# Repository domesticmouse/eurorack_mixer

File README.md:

# Eurorack Mixer

This is a Eurorack module for mixing signals, using a
[TL074](https://www.ti.com/product/TL074).
It is based on the ES x MKI mixer.

**Note:** This is a learning exercise.

[KiCanvas rendering of the mainboard](https://kicanvas.org/?github=https%3A%2F%2Fgithub.com%2Fdomesticmouse%2Feurorack_mixer%2Ftree%2Fmain%2Fhardware%2Fmainboard)

## Parts

| LCSC Part | Name | Description |
| --- | --- | --- |
| [C55071](https://www.lcsc.com/product-detail/C55071.html) | BOURNS 3224W-1-203E | POT 20kΩ 250mW SMD-3P,4.8x3.5mm |
| [C12594](https://www.lcsc.com/product-detail/C12594.html) | TI TL074CDR | LOW-NOISE JFET-INPUT OPERATIONAL AMPLIFIERS |
| [C311666](https://www.lcsc.com/product-detail/C311666.html) | Lelon OVK470M1ETR-0606 | CAP ALUM POLY 47uF ±20% 25V SMD |
| [C49678](https://www.lcsc.com/product-detail/C49678.html) | YAGEO CC0805KRX7R9BB104 | CAP CER 100nF 50V X7R 0805 |
| [C64982](https://www.lcsc.com/product-detail/C64982.html) | MDD(Microdiode Semiconductor) B340A | DIODE SCHOTTKY 40V SMA(DO-214AC) |
| [C19171391](https://www.lcsc.com/product-detail/C19171391.html) | YONGYUTAI YLED0805R | LED RED 0805 SMD |
| [C82544](https://www.lcsc.com/product-detail/C82544.html) | DIODES 1N5819HW-7-F | 25A 1 Independent 40V 450mV@1A 1A SOD-123 Single Diodes |
| [C573025](https://www.lcsc.com/product-detail/C573025.html) | Eurorack Power Connector | CONN IDC HEADER TH 10POS 2.54mm |
| [C17513](https://www.lcsc.com/product-detail/C17513.html) | UNI-ROYAL 0805W8F1001T5E | RES 1kΩ ±1% 125mW 0805 |
| [C149504](https://www.lcsc.com/product-detail/C149504.html) | UNI-ROYAL 0805W8F1003T5E | RES 100kΩ ±1% 125mW 0805 |
| [C17593](https://www.lcsc.com/product-detail/C17593.html) | UNI-ROYAL 0805W8F2702T5E | RES 27kΩ ±1% 125mW 0805 |
| [C17903](https://www.lcsc.com/product-detail/C17903.html) | UNI-ROYAL 1206W4F100JT5E | RES 10Ω ±1% 250mW 1206 |

## Sources

- [AI002 DIY Synthesizer Mixer Module Build Guide](https://aisynthesis.com/ai002-diy-eurorack-mixer-module-build/)
- [AI002 Schematic](https://aisynthesis.com/wp-content/uploads/2018/10/AI002-Mixer-Schematic-2.pdf)
- [ES x MKI EDU DIY Mixer](https://www.ericasynths.lv/shop/diy-kits-1/edu-diy-mixer/)
- [ES x MKI EDU DIY Mixer Manual](https://www.ericasynths.lv/media/MIXER_MANUAL.pdf)
- [Moritz Klein](https://www.youtube.com/@MoritzKlein0)'s
  [Designing a 3-channel mixer with diode distortion from scratch](https://www.youtube.com/watch?v=q8tmUgaXrEQ)
- [TL074 data sheet](https://www.ti.com/lit/ds/symlink/tl074.pdf)
- [EuroRack dimensions](https://midisoft.de/EuroRackDimensions/EuroRack_Dimensions.html)
- [Eurorack Panel Dimensions](https://www.exploding-shed.com/manuals-tutorials/manuals/standards-of-eurorack/eurorack-dimensions/)
- [Doepfer A100 DIY](https://doepfer.de/DIY/a100_diy.htm)
- [benjiaomodular](https://benjiaomodular.com/)'s [MiniAttenuMix](https://benjiaomodular.com/post/2023-11-08-miniattenumix/)

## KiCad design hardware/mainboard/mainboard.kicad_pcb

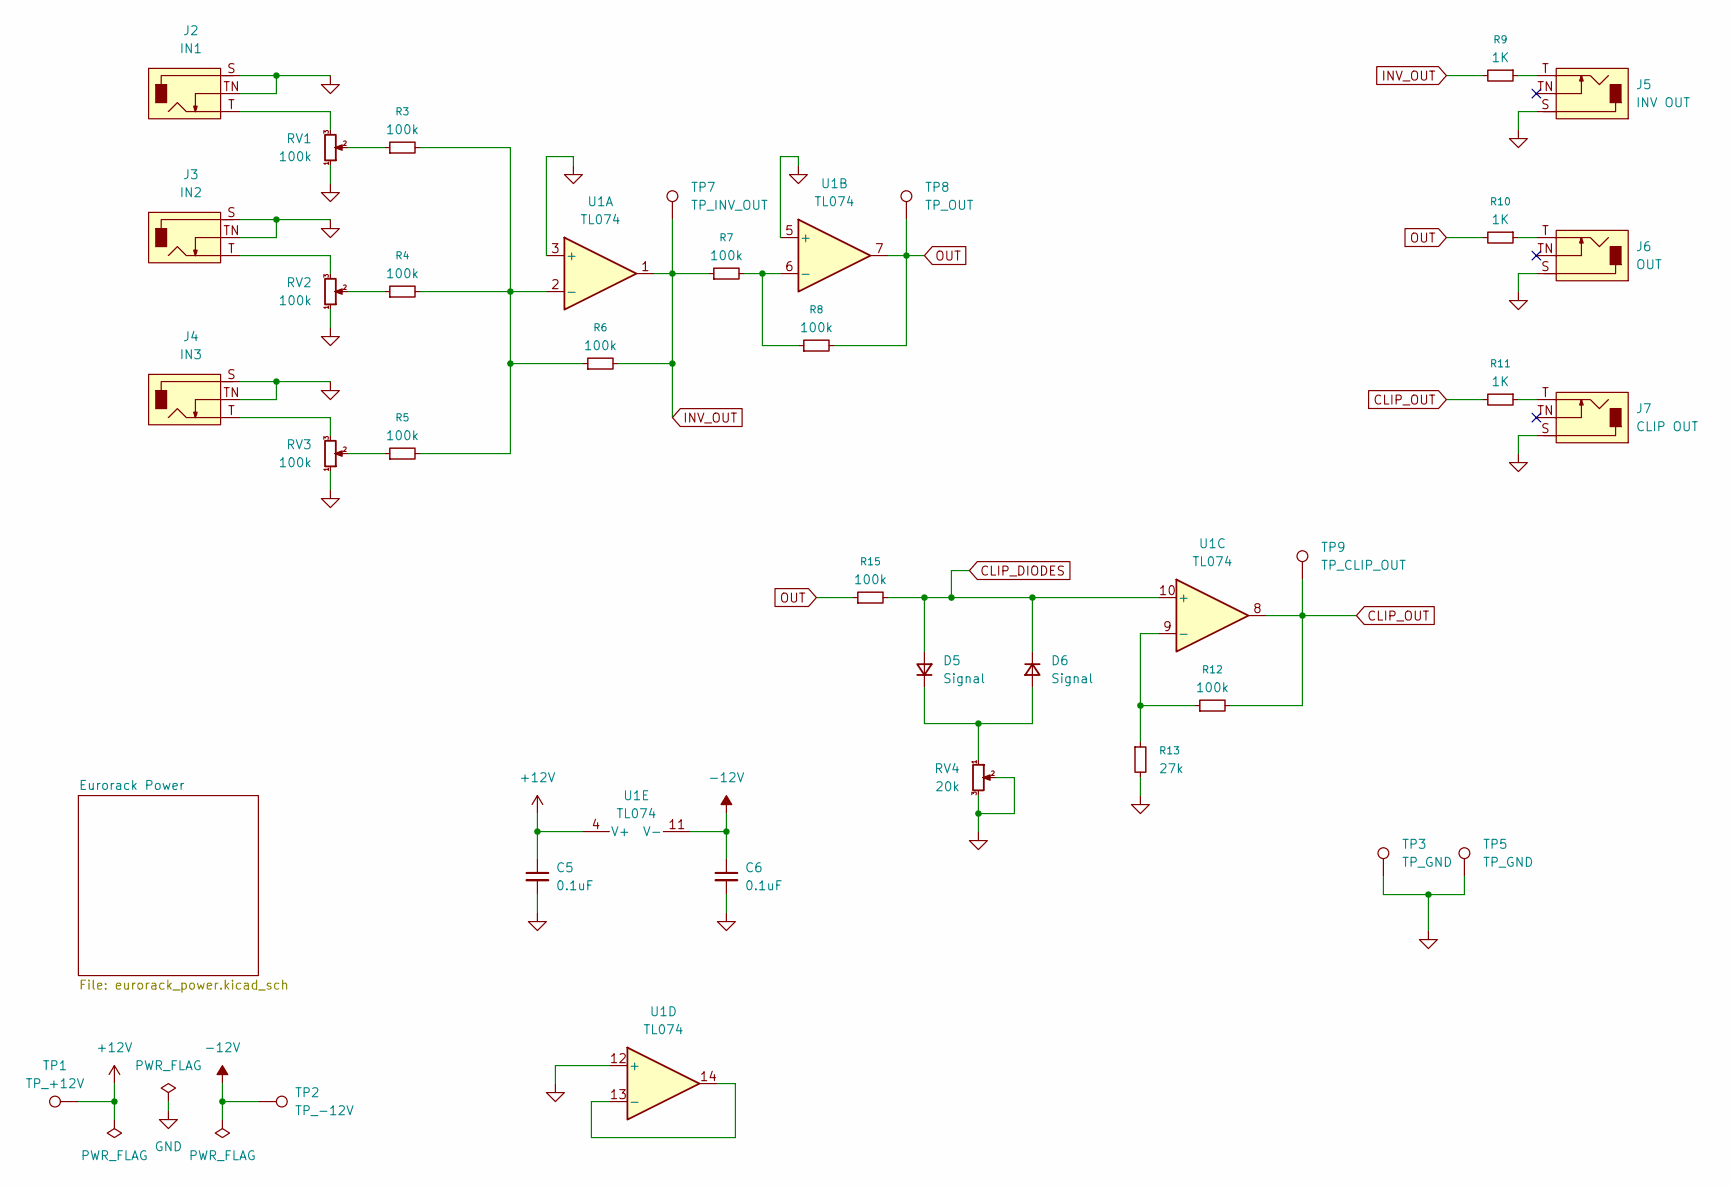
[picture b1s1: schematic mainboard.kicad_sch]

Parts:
C5, C6: 0.1uF; C_0805_2012Metric_Pad1.18x1.45mm_HandSolder; Manufacturer_Part_No CC0805KRX7R9BB104; LCSC_Part_No C49678
D5, D6: Signal; D_SOD-123; Manufacturer_Part_No 1N5819HW-7-F; LCSC_Part_No C82544
J2: IN1; Jack_3.5mm_WQP-PJ398SM_Vertical_Tight
J3: IN2; Jack_3.5mm_WQP-PJ398SM_Vertical_Tight
J4: IN3; Jack_3.5mm_WQP-PJ398SM_Vertical_Tight
J5: INV OUT; Jack_3.5mm_WQP-PJ398SM_Vertical_Tight
J6: OUT; Jack_3.5mm_WQP-PJ398SM_Vertical_Tight
J7: CLIP OUT; Jack_3.5mm_WQP-PJ398SM_Vertical_Tight
R3, R4, R5, R6, R7, R8, R12, R15: 100k; R_0805_2012Metric_Pad1.20x1.40mm_HandSolder; Manufacturer_Part_No 0805W8F1003T5E; LCSC_Part_No C149504
R9, R10, R11: 1K; R_0805_2012Metric_Pad1.20x1.40mm_HandSolder; Manufacturer_Part_No 0805W8F1001T5E; LCSC_Part_No C17513
R13: 27k; R_0805_2012Metric_Pad1.20x1.40mm_HandSolder; Manufacturer_Part_No 0805W8F2702T5E; LCSC_Part_No C17593
RV1, RV2, RV3: 100k; Potentiometer_Alpha_RD901F-40-00D_Single_Vertical
RV4: 20k; Potentiometer_Bourns_3224W_Vertical; Manufacturer_Part_No 3224W-1-203E; LCSC_Part_No C55071
TP1: TP_+12V; TestPoint_Keystone_5000-5004_Miniature; Manufacturer_Part_No RH-5001; LCSC_Part_No C5199801
TP2: TP_-12V; TestPoint_Keystone_5000-5004_Miniature; Manufacturer_Part_No RH-5001; LCSC_Part_No C5199801
TP3, TP5: TP_GND; TestPoint_Keystone_5000-5004_Miniature; Manufacturer_Part_No RH-5001; LCSC_Part_No C5199801
TP7: TP_INV_OUT; TestPoint_Keystone_5000-5004_Miniature; Manufacturer_Part_No RH-5001; LCSC_Part_No C5199801
TP8: TP_OUT; TestPoint_Keystone_5000-5004_Miniature; Manufacturer_Part_No RH-5001; LCSC_Part_No C5199801
TP9: TP_CLIP_OUT; TestPoint_Keystone_5000-5004_Miniature; Manufacturer_Part_No RH-5001; LCSC_Part_No C5199801
U1: TL074; SOIC-14_3.9x8.7mm_P1.27mm; Manufacturer_Part_No TL074CDR; LCSC_Part_No C12594

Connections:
+12V: C5.1, TP1.1, U1.4 (V+); also elsewhere on the board
-12V: C6.1, TP2.1, U1.11 (V-); also elsewhere on the board
CLIP_DIODES: D5.2 (A), D6.1 (K), R15.2, U1.10 (+)
CLIP_OUT: R11.2, R12.2, TP9.1, U1.8
GND: C5.2, C6.2, J2.S, J2.TN, J3.S, J3.TN, J4.S, J4.TN, J5.S, J6.S, J7.S, R13.2, RV1.1, RV2.1, RV3.1, RV4.2, RV4.3, TP3.1, TP5.1, U1.3 (+), U1.5 (+), U1.12 (+); also elsewhere on the board
INV_OUT: R6.2, R7.1, R9.2, TP7.1, U1.1
unnamed: D5.1 (K), D6.2 (A), RV4.1
unnamed: J2.T, RV1.3
unnamed: J3.T, RV2.3
unnamed: J4.T, RV3.3
unnamed: J5.T, R9.1
unnamed: J6.T, R10.1
unnamed: J7.T, R11.1
unnamed: R3.1, RV1.2
unnamed: R4.1, RV2.2
unnamed: R5.1, RV3.2
unnamed: R3.2, R4.2, R5.2, R6.1, U1.2 (-)
unnamed: R7.2, R8.1, U1.6 (-)
unnamed: R12.1, R13.1, U1.9 (-)
unnamed: U1.13 (-), U1.14
OUT: R8.2, R10.2, R15.1, TP8.1, U1.7

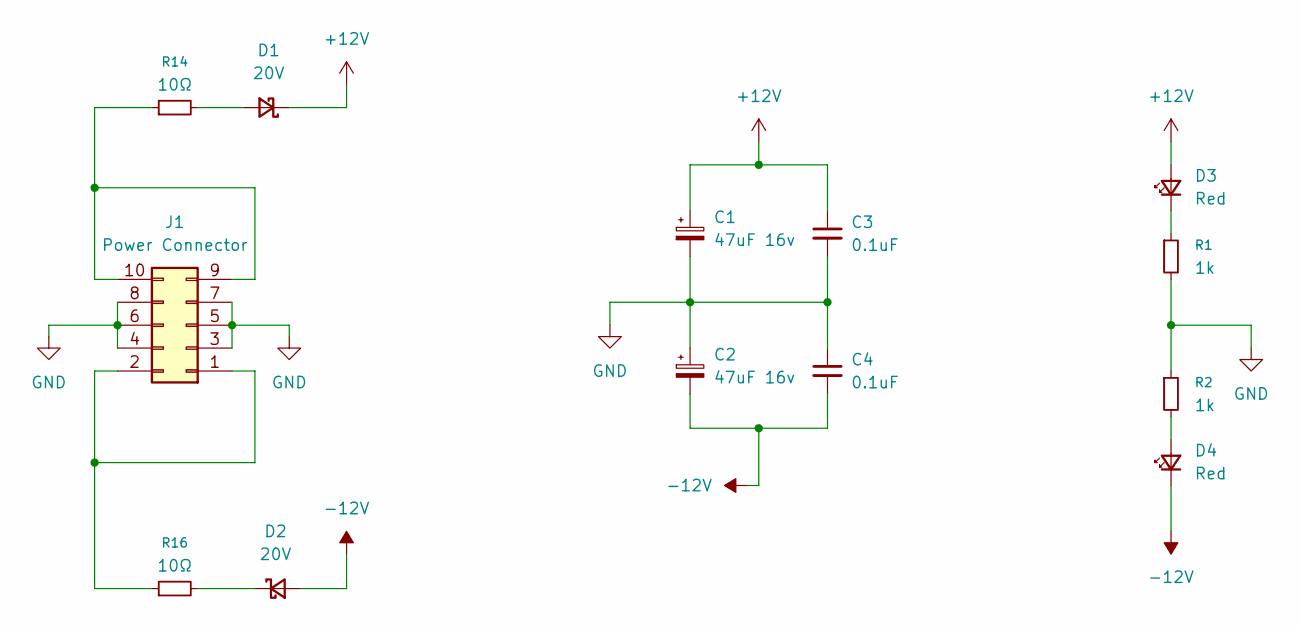
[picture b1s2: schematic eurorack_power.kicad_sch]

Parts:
C1, C2: 47uF 16v; CP_Elec_6.3x5.9; Manufacturer_Part_No OVK470M1ETR-0606; LCSC_Part_No C311666
C3, C4: 0.1uF; C_0805_2012Metric_Pad1.18x1.45mm_HandSolder; Manufacturer_Part_No CC0805KRX7R9BB104; LCSC_Part_No C49678
D1, D2: 20V; D_SOD-323F; Manufacturer_Part_No BAT46WJ,115; LCSC_Part_No C114696
D3, D4: Red; LED_0805_2012Metric_Pad1.15x1.40mm_HandSolder; Manufacturer_Part_No YLED0805R; LCSC_Part_No C19171391
J1: Power Connector; IDC-Header_2x05_P2.54mm_Vertical; Manufacturer_Part_No 1761681-3; LCSC_Part_No C573025
R1, R2: 1k; R_0805_2012Metric_Pad1.20x1.40mm_HandSolder; Manufacturer_Part_No 0805W8F1001T5E; LCSC_Part_No C17513
R14, R16: 10Ω; R_1206_3216Metric_Pad1.30x1.75mm_HandSolder

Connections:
+12V: C1.1, C3.1, D1.1 (K), D3.2 (A); also elsewhere on the board
-12V: C2.2, C4.2, D2.2 (A), D4.1 (K); also elsewhere on the board
GND: C1.2, C2.1, C3.2, C4.1, J1.3, J1.4, J1.5, J1.6, J1.7, J1.8, R1.2, R2.1; also elsewhere on the board
unnamed: D1.2 (A), R14.2
unnamed: D2.1 (K), R16.2
unnamed: D3.1 (K), R1.1
unnamed: D4.2 (A), R2.2
unnamed: J1.1, J1.2, R16.1
unnamed: J1.9, J1.10, R14.1

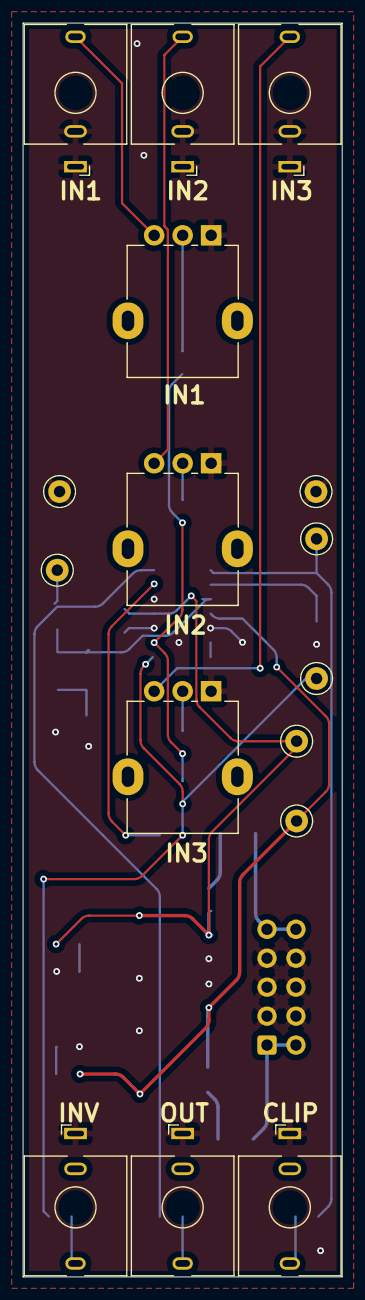
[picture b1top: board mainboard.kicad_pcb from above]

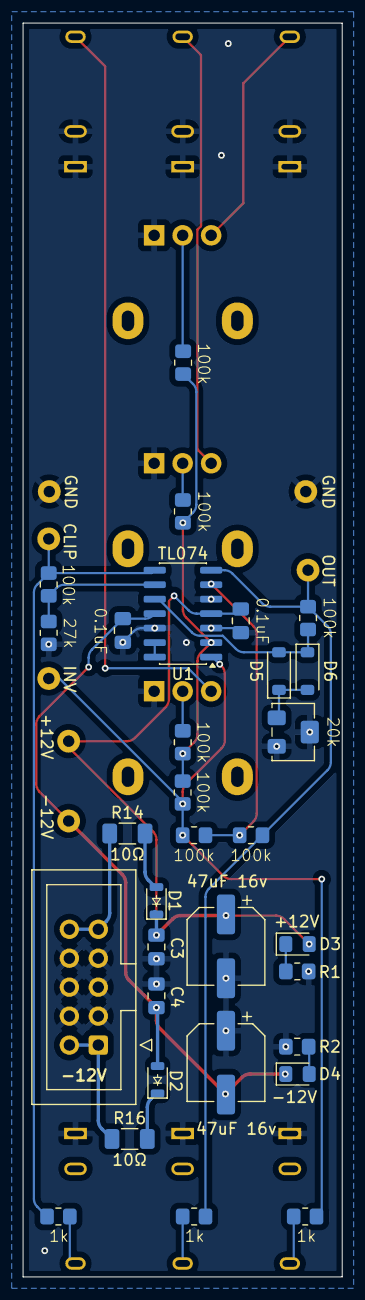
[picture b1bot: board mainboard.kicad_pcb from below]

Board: 2 copper layers, 28.0 x 110.0 mm, 47 parts (31 on the bottom side), 27 nets.

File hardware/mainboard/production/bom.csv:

Designator,Footprint,Quantity,Value,LCSC Part #
"C1, C2",CP_Elec_6.3x5.9,2,47uF 16v,
"C3, C4, C5, C6",0805,4,0.1uF,
"D1, D2",D_SOD-323F,2,20V,
"D3, D4",0805,2,Red,
"D5, D6",D_SOD-123,2,Signal,
J1,IDC-Header_2x05_P2.54mm_Vertical,1,Power Connector,
"R1, R10, R11, R2, R9",0805,5,1k,
"R12, R15, R3, R4, R5, R6, R7, R8",0805,8,100k,
R13,0805,1,27k,
"R14, R16",1206,2,10Ω,
RV4,Potentiometer_Bourns_3224W_Vertical,1,20k,
TP1,TestPoint_Keystone_5000-5004_Miniature,1,TP_+12V,
TP2,TestPoint_Keystone_5000-5004_Miniature,1,TP_-12V,
"TP3, TP5",TestPoint_Keystone_5000-5004_Miniature,2,TP_GND,
TP7,TestPoint_Keystone_5000-5004_Miniature,1,TP_INV_OUT,
TP8,TestPoint_Keystone_5000-5004_Miniature,1,TP_OUT,
TP9,TestPoint_Keystone_5000-5004_Miniature,1,TP_CLIP_OUT,
U1,SOIC-14_3.9x8.7mm_P1.27mm,1,TL074,

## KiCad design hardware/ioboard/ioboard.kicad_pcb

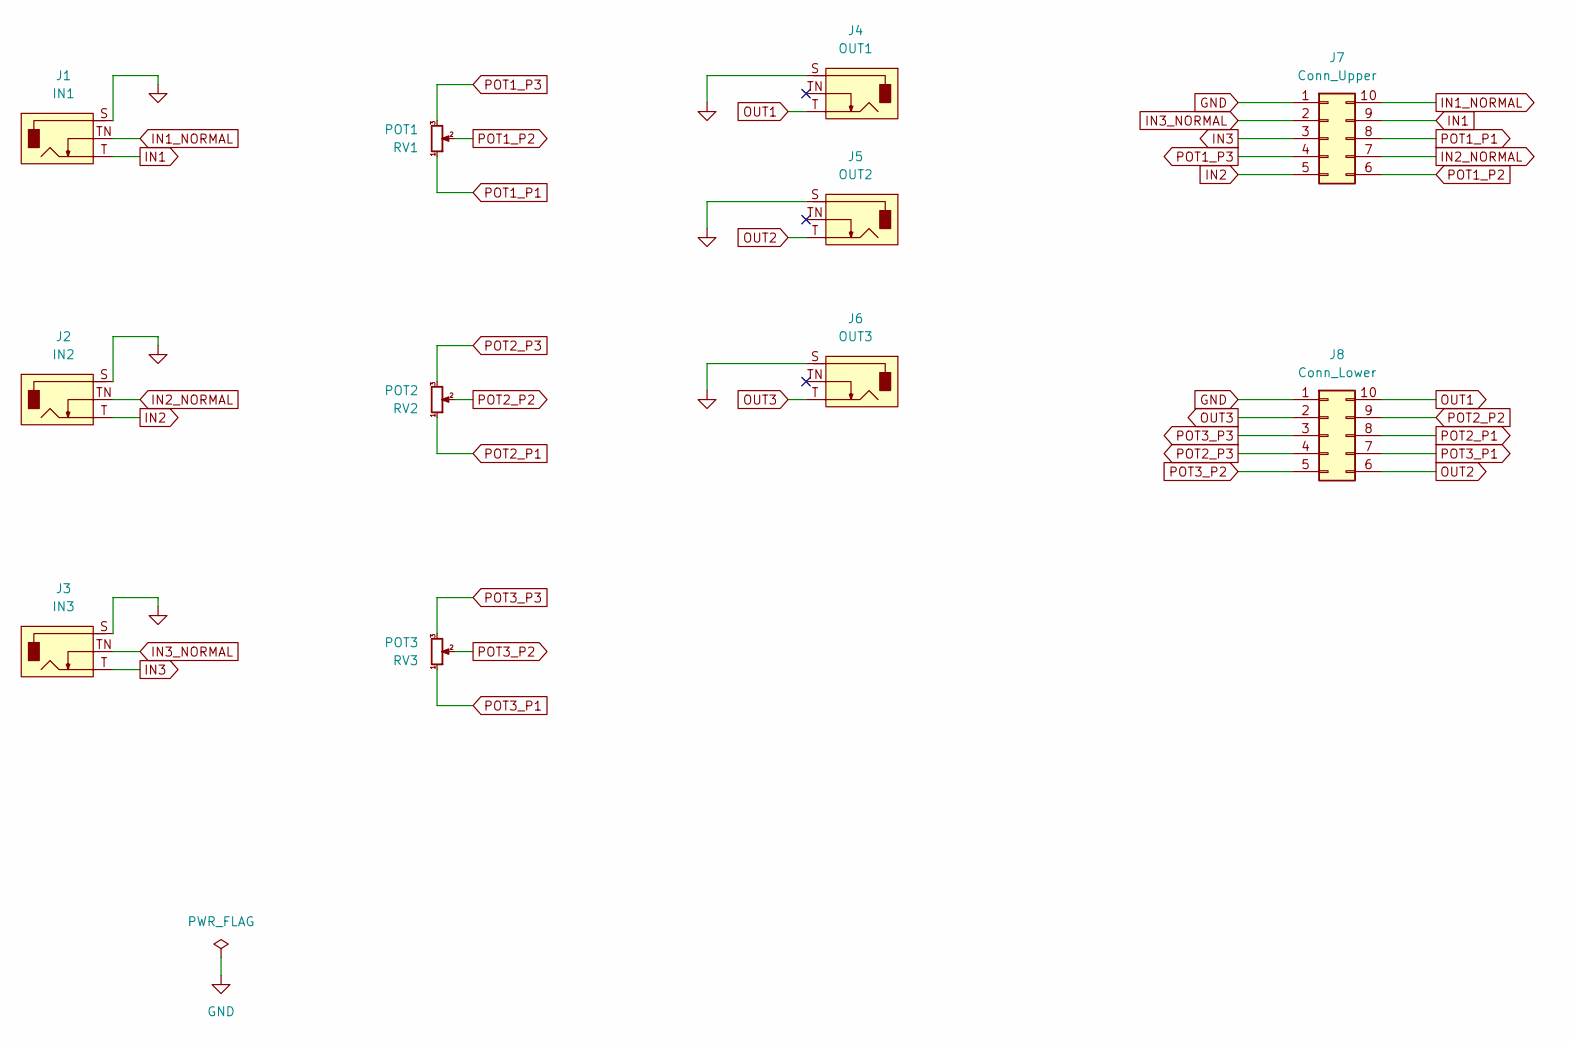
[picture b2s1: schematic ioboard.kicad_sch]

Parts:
J1: IN1; Jack_3.5mm_WQP-PJ398SM_Vertical_Tight
J2: IN2; Jack_3.5mm_WQP-PJ398SM_Vertical_Tight
J3: IN3; Jack_3.5mm_WQP-PJ398SM_Vertical_Tight
J4: OUT1; Jack_3.5mm_WQP-PJ398SM_Vertical_Tight
J5: OUT2; Jack_3.5mm_WQP-PJ398SM_Vertical_Tight
J6: OUT3; Jack_3.5mm_WQP-PJ398SM_Vertical_Tight
J7: Conn_Upper; PinSocket_2x05_P2.54mm_Vertical_SMD
J8: Conn_Lower; PinSocket_2x05_P2.54mm_Vertical_SMD
RV1: POT1; Potentiometer_Alpha_RD901F-40-00D_Single_Vertical
RV2: POT2; Potentiometer_Alpha_RD901F-40-00D_Single_Vertical
RV3: POT3; Potentiometer_Alpha_RD901F-40-00D_Single_Vertical

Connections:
GND: J1.S, J2.S, J3.S, J4.S, J5.S, J6.S, J7.1, J8.1
IN1: J1.T, J7.9
IN1_NORMAL: J1.TN, J7.10
IN2: J2.T, J7.5
IN2_NORMAL: J2.TN, J7.7
IN3: J3.T, J7.3
IN3_NORMAL: J3.TN, J7.2
OUT1: J4.T, J8.10
OUT2: J5.T, J8.6
OUT3: J6.T, J8.2
POT1_P1: J7.8, RV1.1
POT1_P2: J7.6, RV1.2
POT1_P3: J7.4, RV1.3
POT2_P1: J8.8, RV2.1
POT2_P2: J8.9, RV2.2
POT2_P3: J8.4, RV2.3
POT3_P1: J8.7, RV3.1
POT3_P2: J8.5, RV3.2
POT3_P3: J8.3, RV3.3

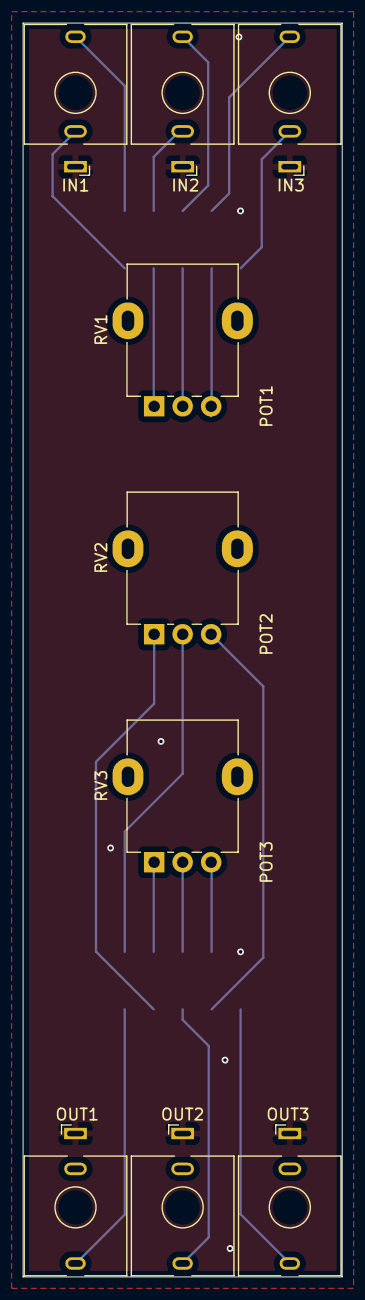
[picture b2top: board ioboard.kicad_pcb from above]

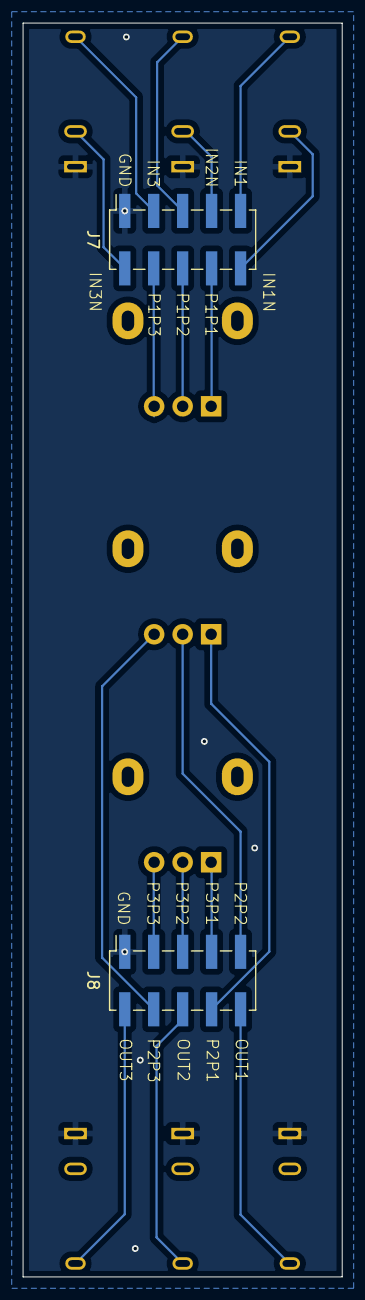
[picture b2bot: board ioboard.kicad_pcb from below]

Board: 2 copper layers, 28.0 x 110.0 mm, 11 parts (2 on the bottom side), 19 nets.

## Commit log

2025-11-25 Add power supply circuitry
2025-11-25 Add PJ398
2025-11-25 Add mixer circuitry
2025-11-25 Add footprints
2025-11-25 Add part list
2025-11-25 Layout
2025-11-25 Clean up
2025-11-26 Add resistors
2025-11-26 Tidyup
2025-11-26 Add KiCanvas to the mix
2025-11-26 Cleanup
2025-11-26 Sent mainboard
2025-11-26 Faceplate
2025-11-27 add measurements
2025-11-27 Add adornment to the faceplate
2025-12-04 Up size the faceplate drill size for the pots
2025-12-04 Add 10Ω resistors to power rails
2025-12-06 Make SOD323F footprint easier to hand solder
2025-12-08 Add ioboard
2025-12-08 Add link to benjiaomodular's MiniAttenuMix
2025-12-09 Update `ioboard`
2025-12-09 Add labels
2025-12-10 Update dimensions
2025-12-10 Start of mixerboard
2025-12-11 Update the barrier diode
2025-12-11 Add Eurorack power
2025-12-20 Re-arrange things
2025-12-22 remove `ioboard` and `mixerboard`
2025-12-22 Update `mainboard`
